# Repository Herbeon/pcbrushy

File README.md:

# pcbrushy
Pcb keychain of my bird (3.5 year old green cheek conure named Brushy). It's also my first PCB yay!!

# schematic

falstad simulation link: https://www.falstad.com/s.php?s=VXZuTE

# PCB

# features
* Since it was my first time I wanted to keep it simple
* the main thing is a 555 timer that flashes 2 LEDs
* There is also an LED + photoresistor so there's more light when it's...bright (I thought it went the other way around while I was making this oops)
* and a push button at the beginning of the circuit.
* Also has silkscreen art by me on Krita :D and a bit of FR4 art. didn't have time to figure out copper loll

I would have liked to add something to do with the motor (a lil buzz fidget or something) but that didn't happen rip. also the transistors are cool I just couldn't figure out what to do with them (except fix my photoresistor LED).

# BOM
| item | amount |
| :------- | ------: |
| 3V battery cell | 1 |
| 10 uF capacitor | 1 |
| 1k resistor | 3 |
| 4.7k resistor | 1 |
| 47k resistor | 1 |
| photoresistor | 1 |
| LED | 3 |
| push button | 1 |
| 555 timer | 1 |

made by Herby on slack for [Hack club solder!](https://solder.hackclub.com/)

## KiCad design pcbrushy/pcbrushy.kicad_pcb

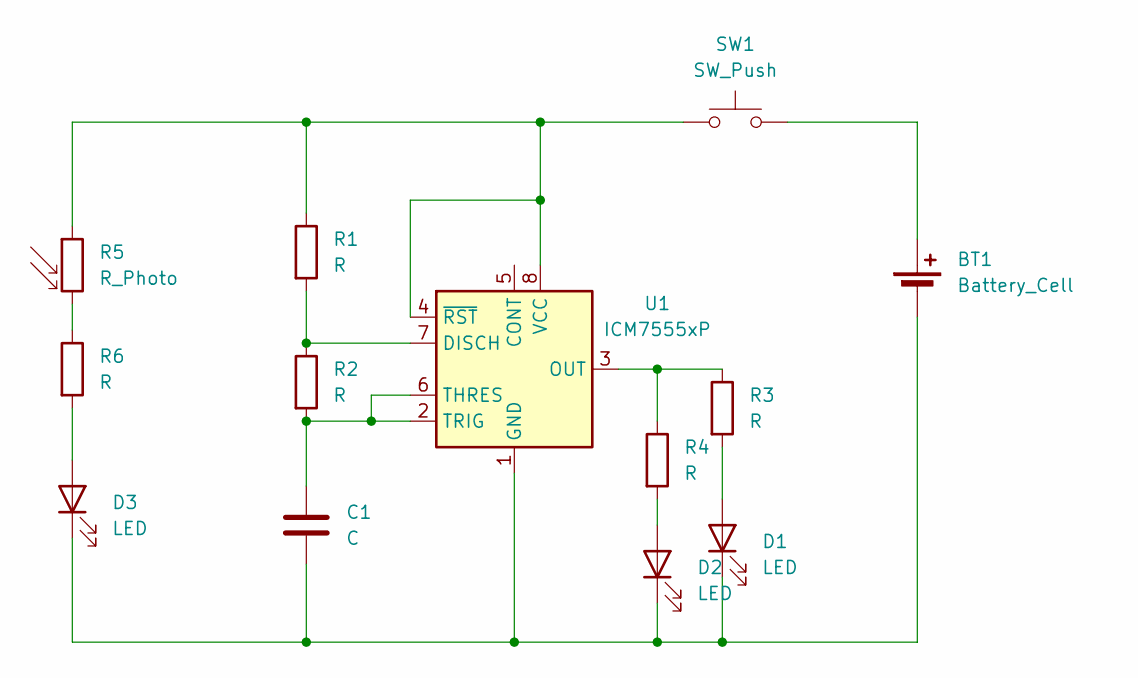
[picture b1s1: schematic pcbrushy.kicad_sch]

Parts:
BT1: Battery_Cell; BatteryHolder_Keystone_3034_1x20mm
C1: C; CP_Radial_D8.0mm_P5.00mm
D1, D2, D3: LED; LED_D5.0mm
R1, R2, R3, R4, R6: R; R_Axial_DIN0207_L6.3mm_D2.5mm_P7.62mm_Horizontal
R5: R_Photo; R_LDR_5.1x4.3mm_P3.4mm_Vertical
SW1: SW_Push; SW_PUSH_6mm
U1: ICM7555xP; DIP-8_W7.62mm

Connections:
unnamed: BT1.1 (+), SW1.2
unnamed: BT1.2 (-), C1.2, D1.1 (K), D2.1 (K), D3.1 (K), U1.1 (GND)
unnamed: D1.2 (A), R3.2
unnamed: D2.2 (A), R4.2
unnamed: D3.2 (A), R6.2
unnamed: R5.2, R6.1
unnamed: R1.2, R2.1, U1.7 (DISCH)
unnamed: R3.1, R4.1, U1.3 (OUT)
unnamed: C1.1, R2.2, U1.2 (TRIG), U1.6 (THRES)
unnamed: R1.1, R5.1, SW1.1, U1.4 (~RST), U1.8 (VCC)

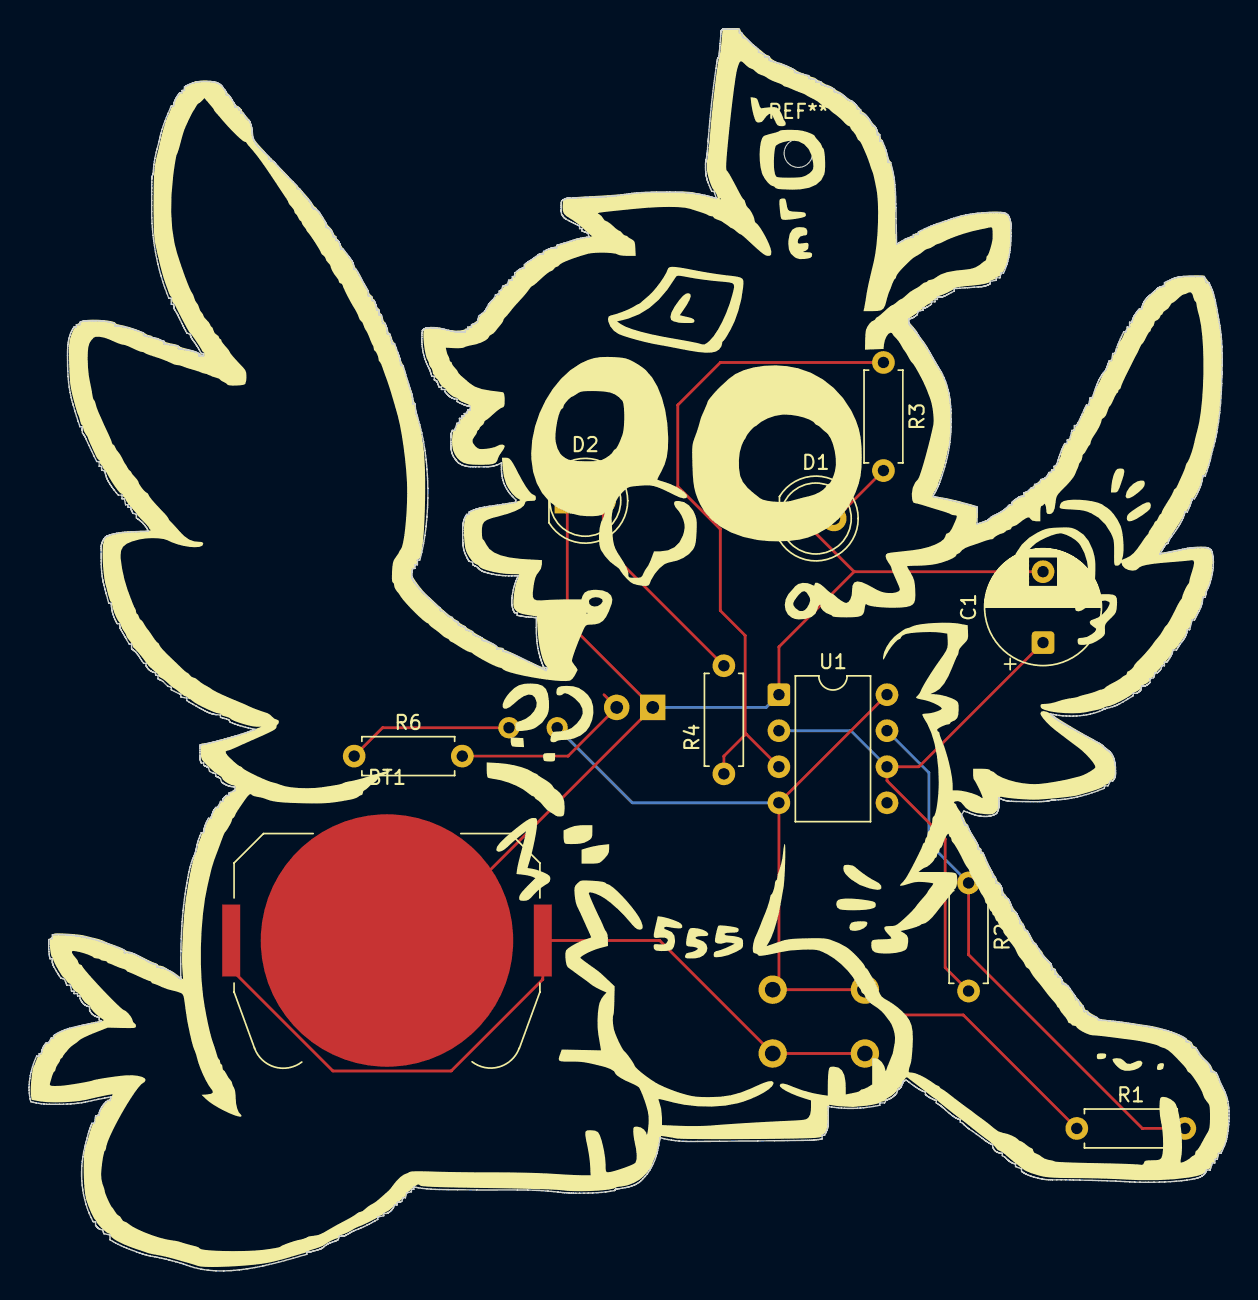
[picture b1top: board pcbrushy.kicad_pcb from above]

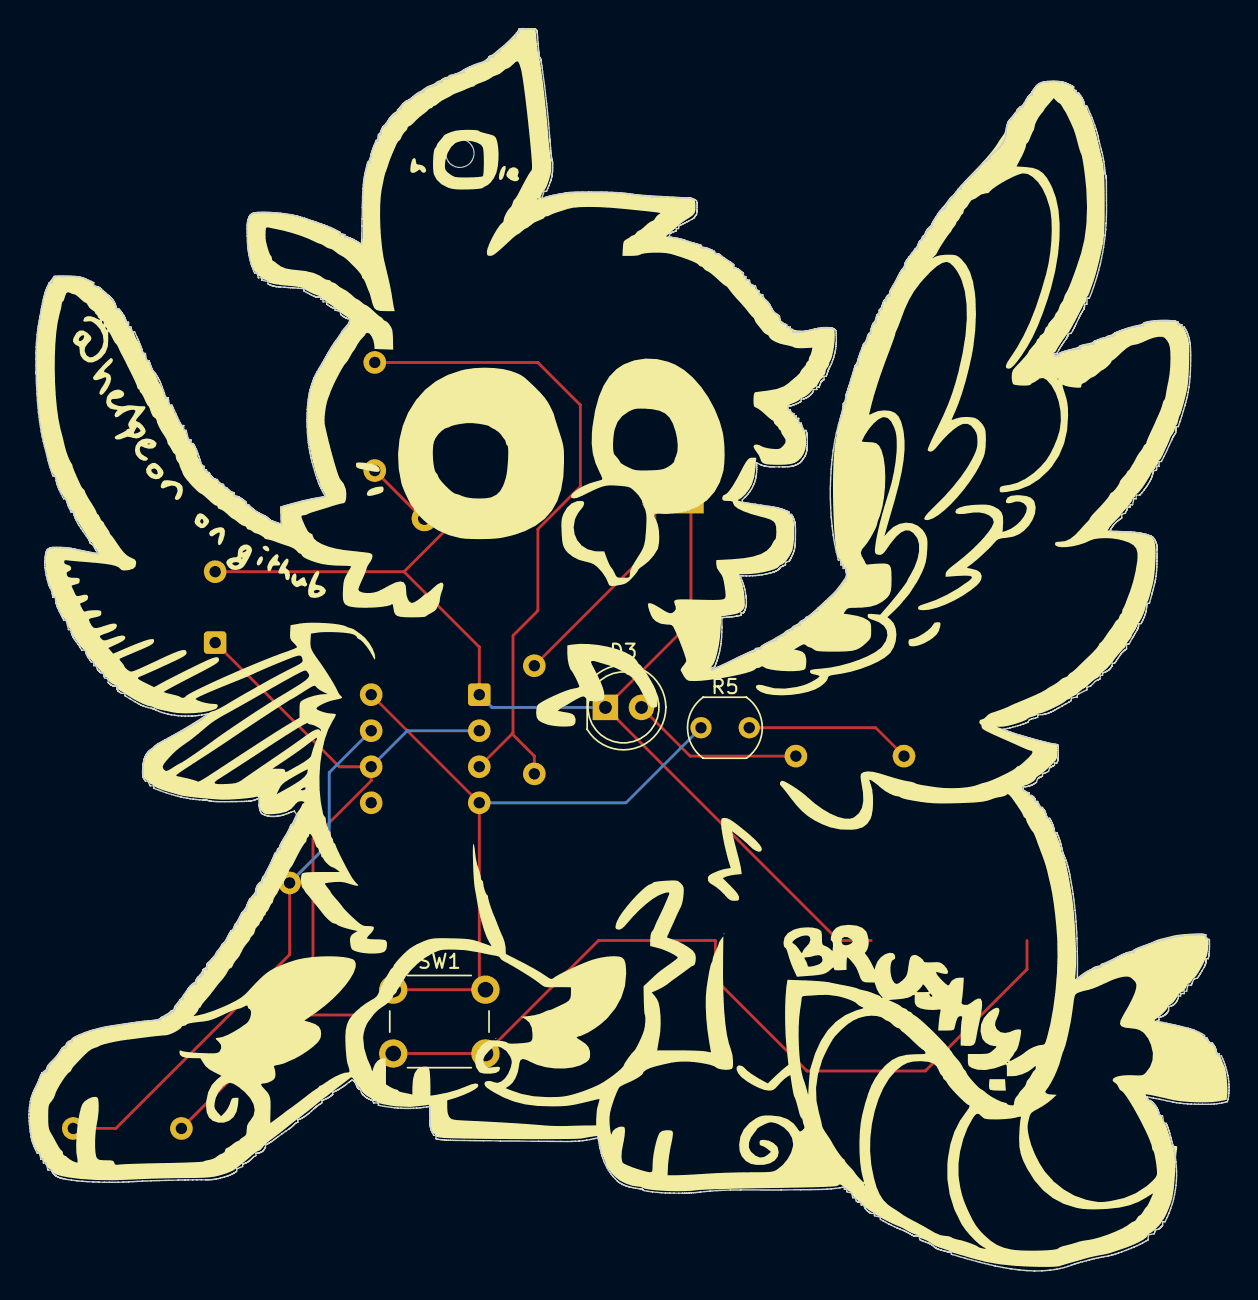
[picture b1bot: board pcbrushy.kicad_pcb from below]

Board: 2 copper layers, 84.6 x 87.5 mm, 14 parts (4 on the bottom side), 10 nets.

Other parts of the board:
.: LOGO
